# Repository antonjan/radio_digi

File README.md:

# radio_digi

This Repository will have the computer sound card to radio interface.
PCB<br>
<br>

PCB<br>
<br>

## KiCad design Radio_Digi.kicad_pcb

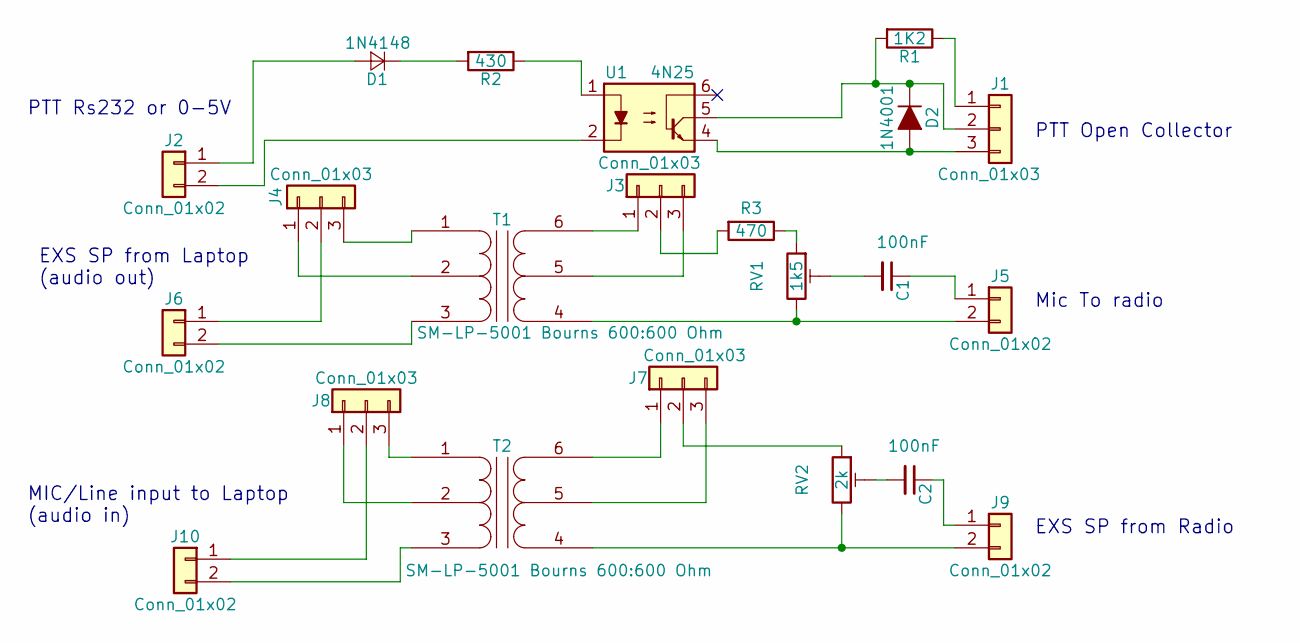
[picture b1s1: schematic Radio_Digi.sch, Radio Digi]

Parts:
C1, C2: 100nF; C_0805_HandSoldering
D1: 1N4148; D_SOD-123
D2: 1N4001; D_SOD-123F
J1: Conn_01x03; TerminalBlock_Philmore_TB133_03x5mm_Straight
J2, J5, J6, J9, J10: Conn_01x02; TerminalBlock_Philmore_TB132_02x5mm_Straight
J3, J4, J7: Conn_01x03; Pin_Header_Straight_1x03_Pitch2.54mm
J8: Conn_01x03; Pin_Header_Straight_1x03_Pitch2.00mm
R1: 1K2; R_0805_HandSoldering
R2: 430; R_0805_HandSoldering
R3: 470; R_0805_HandSoldering
RV1: 1k5; Potentiometer_Bourns_3314G_Vertical
RV2: 2k; Potentiometer_Bourns_3314G_Vertical
T1, T2: SM-LP-5001 Bourns 600:600 Ohm; Transformer_Bourns_SM-LP-5001
U1: 4N25; DIP-6_W7.62mm_SMD

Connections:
unnamed: C1.1, J5.1
unnamed: C1.2, RV1.2
unnamed: C2.1, J9.1
unnamed: C2.2, RV2.2
unnamed: D1.1 (K), R2.2
unnamed: D1.2 (A), J2.1
unnamed: D2.1 (K), J1.2, R1.2, U1.5
unnamed: D2.2 (A), J1.3, U1.4
unnamed: J1.1, R1.1
unnamed: J2.2, U1.2
unnamed: J3.1, T1.6 (S2)
unnamed: J3.2, R3.2
unnamed: J3.3, T1.5 (SE)
unnamed: J4.1, T1.2 (PM)
unnamed: J4.2, J6.1
unnamed: J4.3, T1.1 (PR1)
unnamed: J5.2, RV1.3, T1.4 (S1)
unnamed: J6.2, T1.3 (PR2)
unnamed: J7.1, T2.6 (S2)
unnamed: J7.2, RV2.1
unnamed: J7.3, T2.5 (SE)
unnamed: J8.1, T2.2 (PM)
unnamed: J8.3, T2.1 (PR1)
unnamed: J9.2, RV2.3, T2.4 (S1)
unnamed: J8.2, J10.1
unnamed: J10.2, T2.3 (PR2)
unnamed: R2.1, U1.1
unnamed: R3.1, RV1.1

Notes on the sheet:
Mic To radio
EXS SP from Radio
EXS SP from Laptop (audio out)
MIC/Line input to Laptop (audio in)
PTT Open Collector
PTT Rs232 or 0-5V

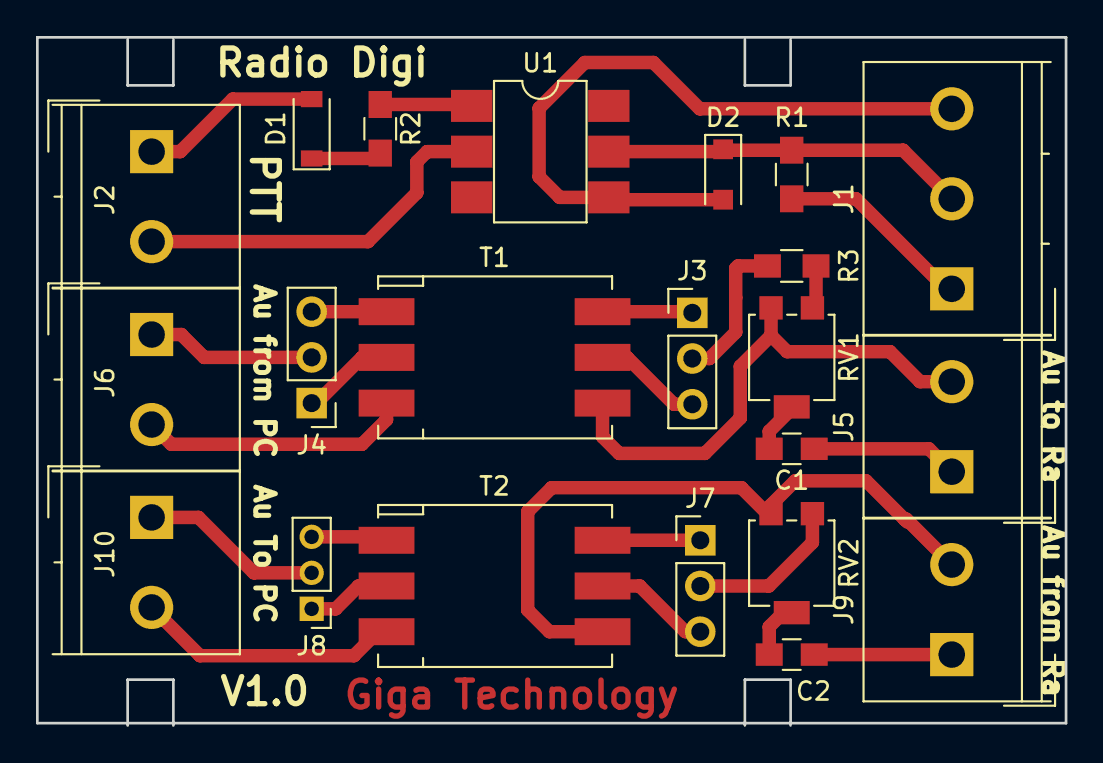
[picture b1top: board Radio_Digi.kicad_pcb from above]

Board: 2 copper layers, 57.1 x 38.2 mm, 22 parts (0 on the bottom side), 28 nets.

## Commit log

2018-08-17 Board Compleet
2018-08-17 Adding diagrams
2018-08-20 Added Diagram
2018-08-29 adding bom
2018-08-30 change led
